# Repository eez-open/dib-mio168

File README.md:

### Ownership and License
The contributors are listed in CONTRIB.TXT.

Licenses | OSHWA UID
--|--
 | 

### Overview

The [EEZ DIB](https://github.com/eez-open/modular-psu) MIO168 module features multiple digital I/O, analog outputs and expansion connectors for carry various AFEs.

### Feature list

* On-board [STM32F446ZCT6](https://www.st.com/content/st_com/en/products/microcontrollers-microprocessors/stm32-32-bit-arm-cortex-mcus/stm32-high-performance-mcus/stm32f4-series/stm32f446/stm32f446zc.html) high-performance foundation line MCU, ARM Cortex-M4 with DSP and FPU, 256 KiB Flash, LQFP-144 package 
* 1 x 8-pin single row 3.81 mm connector (digital inputs)
* 1 x 16-pin dual row 3.81 mm I/O connector (digital and analog outputs)
* 2 x 10-pin ADIB 2.0 mm connectors
* 8 x protected digital inputs (3.3/5/24 V), 2 x fast/slow, 6 x slow
* 8 x digital outputs (low-side) with multiple protections, voltage clamp 42V, current limit 10 A
* 2 x PWM outputs (protected) or sensor bias power (+/-15 V, max. 10 mA)
* 2 x analog bipolar outputs (+/-5 V, +/-10 V, 0-5 V, 0-10 V). Voltage or current output with protection. 12-bit DAC, replaceable with pin compatible 14- or 16-bit version
* 2 x analog bipolar outputs +/-10 V. 12-bit DAC, replaceable with pin compatible 14- or 16-bit version
* On-board isolated power supply with +/-5.3 V outputs (with 4x multipliers), +/-15 V and +3.3 V LDO
* Firmware download via SPI
* Optional SWD for debugging
* I2C EEPROM for storing board specific parameters
* Dimensions: 146 x 95 mm, 4-layer PCB

### r3B1 prototype 3D model (without AFE installed)

### Firmware repository

https://github.com/eez-open/dib-mio168-fw  
The firmware download procedure is described in [Chapter 13.2](https://www.envox.eu/eez-bench-box-3/bb3-user-manual/13-firmware-upgrade/#bb3_man_module_upgrade) of the User Manual.  
The MIO168 module GUI is described in [Chapter 19](https://www.envox.eu/eez-bench-box-3/bb3-user-manual/19-mio168-mixed-input-output-module/) of the User Manual. 

### KiCad project (v7 or newer)

* [MIO168 r3B1](https://github.com/eez-open/dib-mio168/tree/master/EDA%20files/KiCad)

All symbols, footprints and 3D models used in the project can be found in the [EEZ-DIB Library](https://github.com/eez-open/eez-kicad-libraries) plugin for KiCad.

### Bill of materials

* [Download](https://github.com/eez-open/dib-mio168/tree/master/EDA%20files/KiCad/bom/ibom.html) as raw file _Interactive BOM_ (ibom.html) and open it locally in your browser.

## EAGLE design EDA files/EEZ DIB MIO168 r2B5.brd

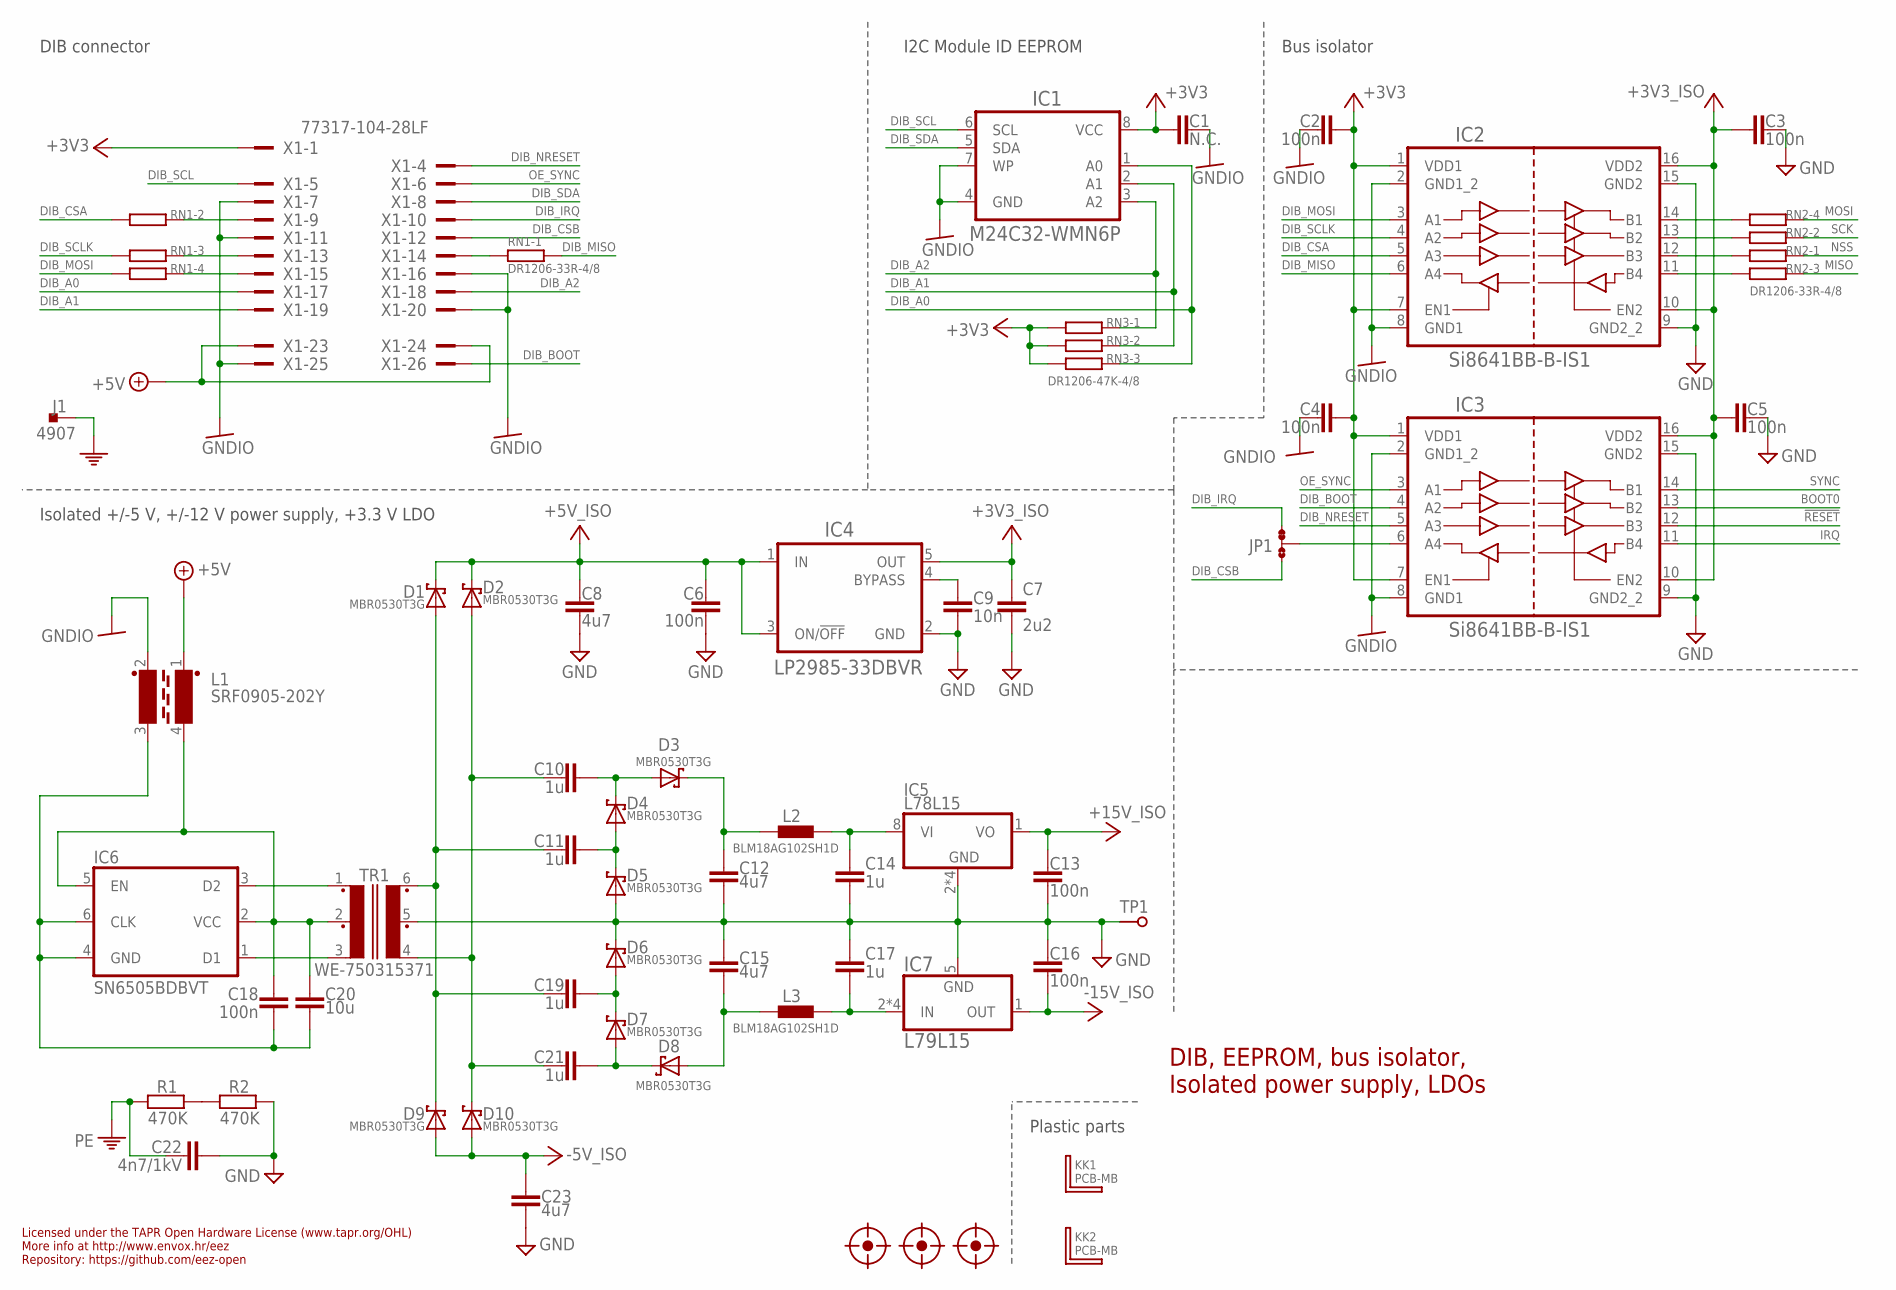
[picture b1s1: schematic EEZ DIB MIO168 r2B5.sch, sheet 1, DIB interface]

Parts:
C1: N.C.; C0603
C2, C3, C4, C5, C6, C13, C16, C18: 100n; C0603
C7: 2u2; C0805
C8, C12, C15, C23: 4u7; C0805
C9: 10n; C0805
C10, C11, C14, C17, C19, C21: 1u; C0805
C20: 10u; C1206
C22: 4n7/1kV; C1812
D1, D2, D3, D4, D5, D6, D7, D8, D9, D10: MBR0530T3G; SOD123
FM1, FM2, FM3: FIDUCIAL_2; FIDUCIAL_DUAL
IC1: M24C32-WMN6P; SOIC127P600X173-8N
IC2, IC3: Si8641BB-B-IS1; SOIC-16
IC4: LP2985-33DBVR; SOT95P270X145-5N
IC5: L78L15; SOIC127P600X173-8N
IC6: SN6505BDBVT; DBV0006A_N
IC7: L79L15; SOIC127P600X173-8N
J1: 4907; PCB_TAB-4907
JP1: JP3-CUT-0805-ROTATED; JP3-0805-CUT2
KK1, KK2: PCB-MB
L1: SRF0905-202Y; SRF0905
L2, L3: BLM18AG102SH1D; BEAD0603
R1, R2: 470K; R0805
RN1, RN2: DR1206-33R-4/8; CAY16
RN3: DR1206-47K-4/8; CAY16
TP1: PCB_TEST_TABSHIELD; PCB_SHIELD_TAB
TR1: WE-750315371; MURATA_78615
X1: 77317-104-28LF

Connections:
!RESET: IC3.12 (B3); also elsewhere on the board
+3V3: C1.2, C2.1, C4.1, IC1.8 (VCC), IC2.1 (VDD1), IC2.7 (EN1), IC3.1 (VDD1), IC3.7 (EN1), RN3.6 (2), RN3.7 (2), RN3.8 (2), X1.1
+3V3_ISO: C3.2, C5.2, C7.1, IC2.10 (EN2), IC2.16 (VDD2), IC3.10 (EN2), IC3.16 (VDD2), IC4.5 (OUT); also elsewhere on the board
+5V: L1.1, X1.23, X1.24
+5V_ISO: C6.1, C8.2, D1.C, D2.C, IC4.1 (IN), IC4.3 (ON/!OFF); also elsewhere on the board
+15V_ISO: C13.1, IC5.1 (VO); also elsewhere on the board
-5V_ISO: C23.2, D9.A, D10.A; also elsewhere on the board
-15V_IN: C17.1, IC7.2 (IN), IC7.3 (IN), IC7.6 (IN), IC7.7 (IN), L3.P$2 (2)
-15V_ISO: C16.2, IC7.1 (OUT); also elsewhere on the board
BOOT0: IC3.13 (B2); also elsewhere on the board
DIB_A0: IC1.1 (A0), RN3.3 (1), X1.17
DIB_A1: IC1.2 (A1), RN3.2 (1), X1.19
DIB_A2: IC1.3 (A2), RN3.1, X1.18
DIB_BOOT: IC3.4 (A2), X1.26
DIB_CSA: IC2.5 (A3), RN1.2 (1)
DIB_CSB: JP1.NO, X1.12
DIB_IRQ: JP1.NC, X1.10
DIB_MISO: IC2.6 (A4), RN1.1
DIB_MOSI: IC2.3 (A1), RN1.4 (1)
DIB_NRESET: IC3.5 (A3), X1.4
DIB_SCL: IC1.6 (SCL), X1.5
DIB_SCLK: IC2.4 (A2), RN1.3 (1)
DIB_SDA: IC1.5 (SDA), X1.8
GND: C3.1, C5.1, C6.2, C7.2, C8.1, C9.1, C12.2, C13.2, C14.1, C15.1, C16.1, C17.2, C22.2, C23.1, D5.A, D6.C, IC2.9 (GND2_2), IC2.15 (GND2), IC3.9 (GND2_2), IC3.15 (GND2), IC4.2 (GND), IC5.2 (GND), IC5.3 (GND), IC5.6 (GND), IC5.7 (GND), IC7.5 (GND), R2.2, TP1.1, TR1.5; also elsewhere on the board
GNDIO: C1.1, C2.2, C4.2, IC1.4 (GND), IC1.7 (WP), IC2.2 (GND1_2), IC2.8 (GND1), IC3.2 (GND1_2), IC3.8 (GND1), L1.2, X1.7, X1.11, X1.16, X1.20, X1.25
IRQ: IC3.11 (B4); also elsewhere on the board
MISO: RN2.6 (2); also elsewhere on the board
MOSI: RN2.5 (2); also elsewhere on the board
unnamed: IC3.6 (A4), JP1.COM
unnamed: IC2.14 (B1), RN2.4 (1)
unnamed: R1.2, R2.1
unnamed: C11.1, D4.A, D5.C
unnamed: IC6.3 (D2), TR1.1
unnamed: IC6.1 (D1), TR1.3
unnamed: C11.2, C19.2, D1.A, D9.C, TR1.6
unnamed: RN1.7 (2), X1.9
unnamed: C10.2, C21.2, D2.A, D10.C, TR1.4
unnamed: IC2.11 (B4), RN2.3 (1)
unnamed: C10.1, D3.A, D4.C
unnamed: RN1.6 (2), X1.13
unnamed: RN1.8 (2), X1.14
unnamed: RN1.5 (2), X1.15
unnamed: C19.1, D6.A, D7.C
unnamed: C21.1, D7.A, D8.C
unnamed: C9.2, IC4.4 (BYPASS)
unnamed: C14.2, IC5.8 (VI), L2.P$2 (2)
unnamed: IC2.13 (B2), RN2.2 (1)
unnamed: IC2.12 (B3), RN2.1
unnamed: C15.2, D8.A, L3.P$1 (1)
unnamed: C12.1, D3.C, L2.P$1 (1)
NSS: RN2.8 (2); also elsewhere on the board
OE_SYNC: IC3.3 (A1), X1.6
PE: C22.1, J1.1, J1.2, R1.1
SCK: RN2.7 (2); also elsewhere on the board
SN_GND: C18.2, C20.1, IC6.4 (GND), IC6.6 (CLK), L1.3
SN_VCC: C18.1, C20.2, IC6.2 (VCC), IC6.5 (EN), L1.4, TR1.2
SYNC: IC3.14 (B1); also elsewhere on the board

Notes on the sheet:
Licensed under the TAPR Open Hardware License (www.tapr.org/OHL)
Repository: https://github.com/eez-open
More info at http://www.envox.hr/eez
DIB, EEPROM, bus isolator, Isolated power supply, LDOs
Plastic parts
I2C Module ID EEPROM
Bus isolator
Isolated +/-5 V, +/-12 V power supply, +3.3 V LDO
DIB connector

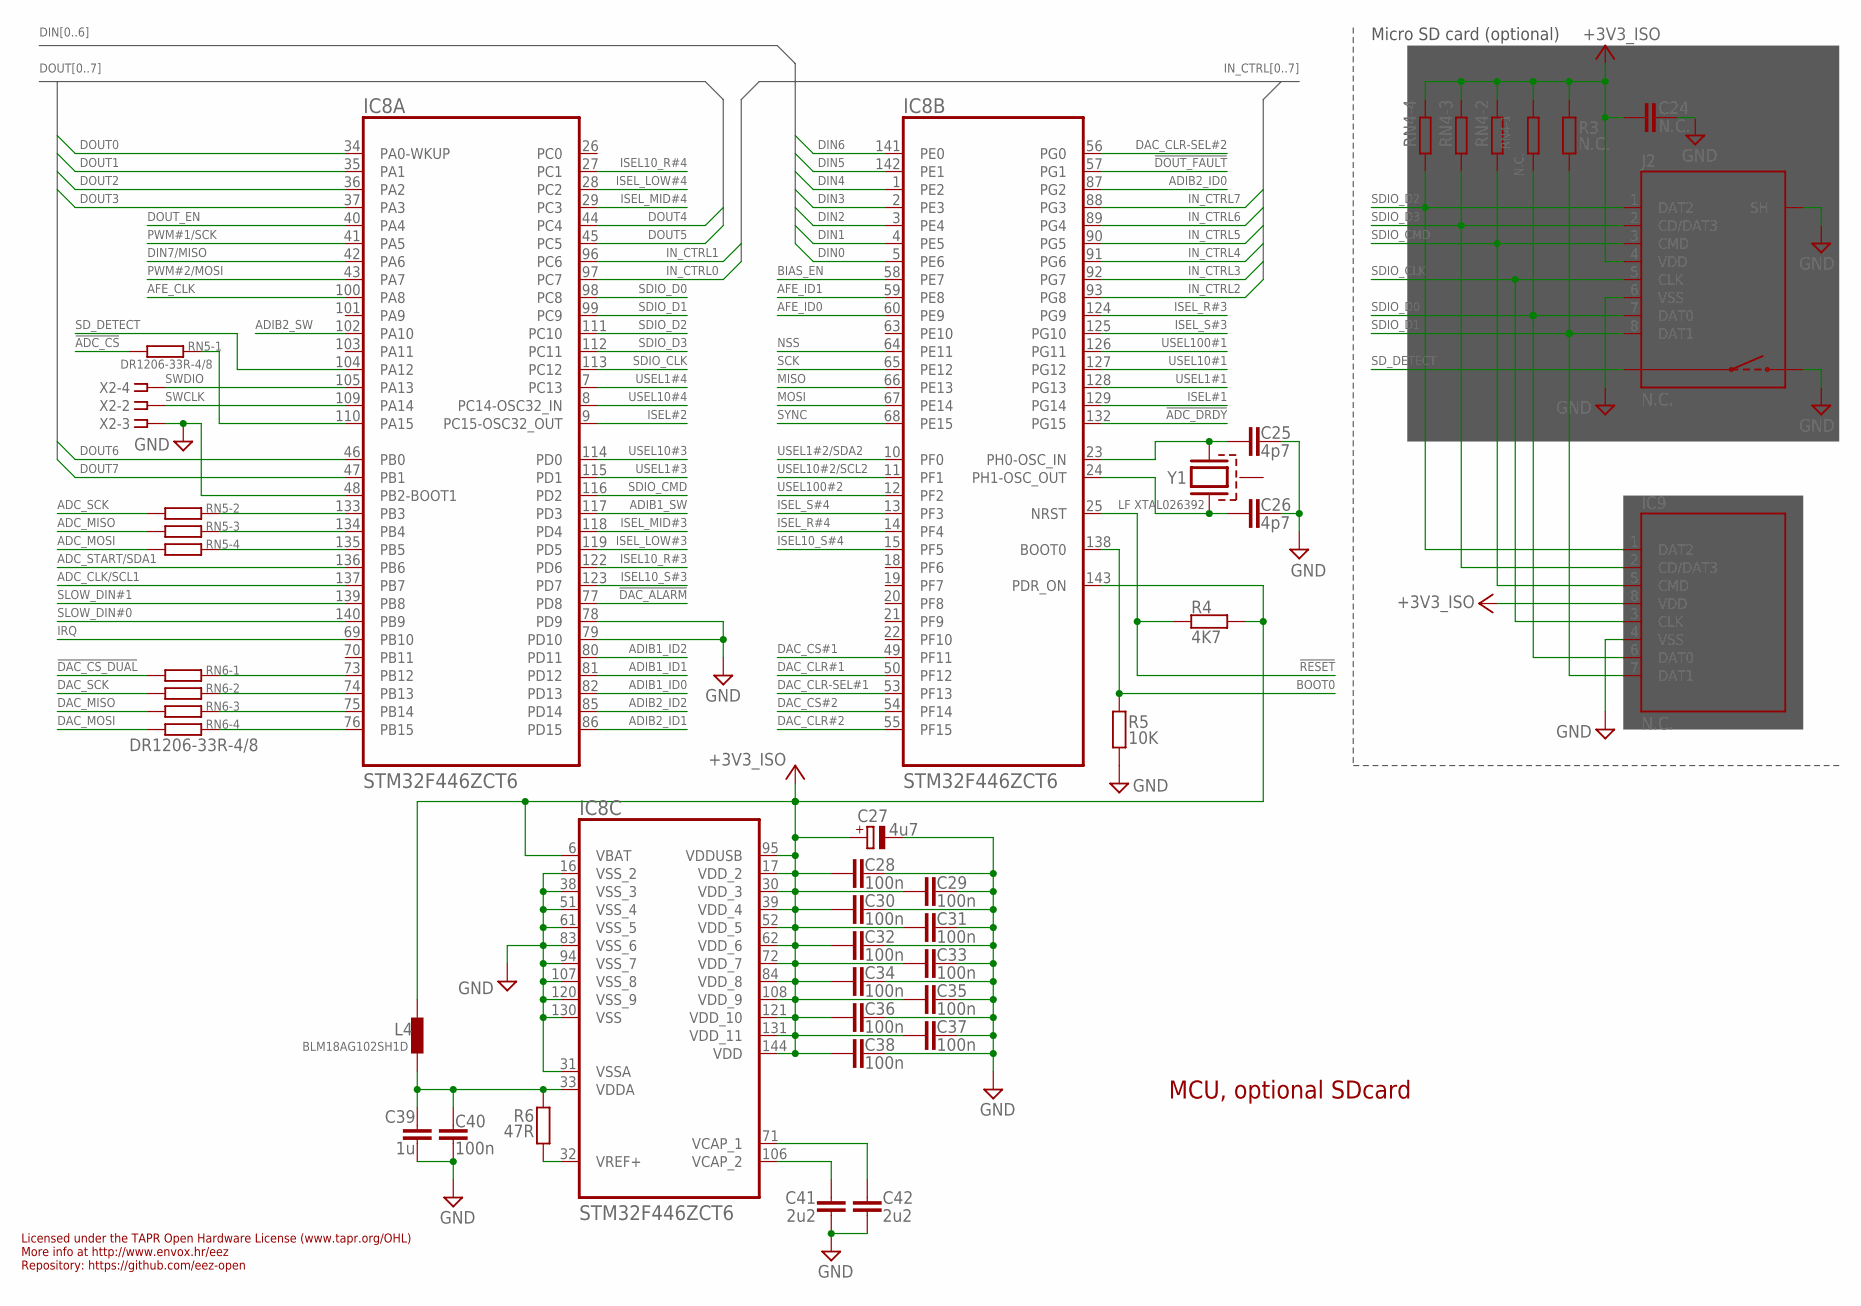
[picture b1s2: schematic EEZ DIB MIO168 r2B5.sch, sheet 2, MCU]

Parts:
C24: N.C.; C0805
C25, C26: 4p7; C0603
C27: 4u7; EC1206
C28, C29, C30, C31, C32, C33, C34, C35, C36, C37, C38, C40: 100n; C0603
C39: 1u; C0805
C41, C42: 2u2; C0805
IC8: STM32F446ZCT6; LQFP-144
IC9: N.C.; LGA8
J2: N.C.; 5033981892
L4: BLM18AG102SH1D; BEAD0603
R3: N.C.; R0805
R4: 4K7; R0805
R5: 10K; R0805
R6: 47R; R0805
RN4: N.C.; CAY16
RN5, RN6: DR1206-33R-4/8; CAY16
X2: N.C.; SSW-106-02-S-S
Y1: LF XTAL026392; 12SMX(B)

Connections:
!ADC_CS: RN5.1; also elsewhere on the board
!ADC_DRDY: IC8.132 (PG15); also elsewhere on the board
!DAC_ALARM: IC8.77 (PD8); also elsewhere on the board
!DAC_CS_DUAL: RN6.1; also elsewhere on the board
!DOUT_FAULT: IC8.57 (PG1); also elsewhere on the board
!RESET: IC8.25 (NRST), R4.2; also elsewhere on the board
+3V3_ISO: C24.1, C27.+, C28.1, C29.1, C30.1, C31.1, C32.1, C33.1, C34.1, C35.1, C36.1, C37.1, C38.1, IC8.6 (VBAT), IC8.17 (VDD_2), IC8.30 (VDD_3), IC8.39 (VDD_4), IC8.52 (VDD_5), IC8.62 (VDD_6), IC8.72 (VDD_7), IC8.84 (VDD_8), IC8.95 (VDDUSB), IC8.108 (VDD_9), IC8.121 (VDD_10), IC8.131 (VDD_11), IC8.143 (PDR_ON), IC8.144 (VDD), IC9.8 (VDD), J2.4 (VDD), L4.P$1 (1), R3.1, R4.1, RN4.1, RN4.2 (1), RN4.3 (1), RN4.4 (1); also elsewhere on the board
ADC_CLK/SCL1: IC8.137 (PB7); also elsewhere on the board
ADC_MISO: RN5.3 (1); also elsewhere on the board
ADC_MOSI: RN5.4 (1); also elsewhere on the board
ADC_SCK: RN5.2 (1); also elsewhere on the board
ADC_START/SDA1: IC8.136 (PB6); also elsewhere on the board
ADIB1_ID0: IC8.82 (PD13); also elsewhere on the board
ADIB1_ID1: IC8.81 (PD12); also elsewhere on the board
ADIB1_ID2: IC8.80 (PD11); also elsewhere on the board
ADIB1_SW: IC8.117 (PD3); also elsewhere on the board
ADIB2_ID0: IC8.87 (PG2); also elsewhere on the board
ADIB2_ID1: IC8.86 (PD15); also elsewhere on the board
ADIB2_ID2: IC8.85 (PD14); also elsewhere on the board
ADIB2_SW: IC8.102 (PA10); also elsewhere on the board
AFE_CLK: IC8.100 (PA8); also elsewhere on the board
AFE_ID0: IC8.60 (PE9); also elsewhere on the board
AFE_ID1: IC8.59 (PE8); also elsewhere on the board
BIAS_EN: IC8.58 (PE7); also elsewhere on the board
BOOT0: IC8.138 (BOOT0), R5.2; also elsewhere on the board
DAC_CLR#1: IC8.50 (PF12); also elsewhere on the board
DAC_CLR#2: IC8.55 (PF15); also elsewhere on the board
DAC_CLR-SEL#1: IC8.53 (PF13); also elsewhere on the board
DAC_CLR-SEL#2: IC8.56 (PG0); also elsewhere on the board
DAC_CS#1: IC8.49 (PF11); also elsewhere on the board
DAC_CS#2: IC8.54 (PF14); also elsewhere on the board
DAC_MISO: RN6.3 (1); also elsewhere on the board
DAC_MOSI: RN6.4 (1); also elsewhere on the board
DAC_SCK: RN6.2 (1); also elsewhere on the board
DIN0: IC8.5 (PE6); also elsewhere on the board
DIN1: IC8.4 (PE5); also elsewhere on the board
DIN2: IC8.3 (PE4); also elsewhere on the board
DIN3: IC8.2 (PE3); also elsewhere on the board
DIN4: IC8.1 (PE2); also elsewhere on the board
DIN5: IC8.142 (PE1); also elsewhere on the board
DIN6: IC8.141 (PE0); also elsewhere on the board
DIN7/MISO: IC8.42 (PA6); also elsewhere on the board
DOUT0: IC8.34 (PA0-WKUP); also elsewhere on the board
DOUT1: IC8.35 (PA1); also elsewhere on the board
DOUT2: IC8.36 (PA2); also elsewhere on the board
DOUT3: IC8.37 (PA3); also elsewhere on the board
DOUT4: IC8.44 (PC4); also elsewhere on the board
DOUT5: IC8.45 (PC5); also elsewhere on the board
DOUT6: IC8.46 (PB0); also elsewhere on the board
DOUT7: IC8.47 (PB1); also elsewhere on the board
DOUT_EN: IC8.40 (PA4); also elsewhere on the board
GND: C24.2, C25.1, C26.1, C27.-, C28.2, C29.2, C30.2, C31.2, C32.2, C33.2, C34.2, C35.2, C36.2, C37.2, C38.2, C39.2, C40.2, C41.1, C42.1, IC8.16 (VSS_2), IC8.31 (VSSA), IC8.38 (VSS_3), IC8.48 (PB2-BOOT1), IC8.51 (VSS_4), IC8.61 (VSS_5), IC8.78 (PD9), IC8.79 (PD10), IC8.83 (VSS_6), IC8.94 (VSS_7), IC8.107 (VSS_8), IC8.120 (VSS_9), IC8.130 (VSS), IC9.4 (VSS), J2.6 (VSS), J2.S (SH), J2.S1 (SH), J2.S2 (SH), J2.SW2, R5.1, X2.3; also elsewhere on the board
IN_CTRL0: IC8.97 (PC7); also elsewhere on the board
IN_CTRL1: IC8.96 (PC6); also elsewhere on the board
IN_CTRL2: IC8.93 (PG8); also elsewhere on the board
IN_CTRL3: IC8.92 (PG7); also elsewhere on the board
IN_CTRL4: IC8.91 (PG6); also elsewhere on the board
IN_CTRL5: IC8.90 (PG5); also elsewhere on the board
IN_CTRL6: IC8.89 (PG4); also elsewhere on the board
IN_CTRL7: IC8.88 (PG3); also elsewhere on the board
IRQ: IC8.69 (PB10); also elsewhere on the board
ISEL10_R#3: IC8.122 (PD6); also elsewhere on the board
ISEL10_R#4: IC8.27 (PC1); also elsewhere on the board
ISEL10_S#3: IC8.123 (PD7); also elsewhere on the board
ISEL10_S#4: IC8.15 (PF5); also elsewhere on the board
ISEL#1: IC8.129 (PG14); also elsewhere on the board
ISEL#2: IC8.9 (PC15-OSC32_OUT); also elsewhere on the board
ISEL_LOW#3: IC8.119 (PD5); also elsewhere on the board
ISEL_LOW#4: IC8.28 (PC2); also elsewhere on the board
ISEL_MID#3: IC8.118 (PD4); also elsewhere on the board
ISEL_MID#4: IC8.29 (PC3); also elsewhere on the board
ISEL_R#3: IC8.124 (PG9); also elsewhere on the board
ISEL_R#4: IC8.14 (PF4); also elsewhere on the board
ISEL_S#3: IC8.125 (PG10); also elsewhere on the board
ISEL_S#4: IC8.13 (PF3); also elsewhere on the board
MISO: IC8.66 (PE13); also elsewhere on the board
MOSI: IC8.67 (PE14); also elsewhere on the board
unnamed: IC8.110 (PA15), RN5.8 (2)
unnamed: IC8.133 (PB3), RN5.7 (2)
unnamed: IC8.134 (PB4), RN5.6 (2)
unnamed: C41.2, IC8.106 (VCAP_2)
unnamed: IC8.135 (PB5), RN5.5 (2)
unnamed: C42.2, IC8.71 (VCAP_1)
unnamed: C39.1, C40.1, IC8.33 (VDDA), L4.P$2 (2), R6.1
unnamed: IC8.32 (VREF+), R6.2
unnamed: IC8.73 (PB12), RN6.8 (2)
unnamed: IC8.74 (PB13), RN6.7 (2)
unnamed: IC8.75 (PB14), RN6.6 (2)
unnamed: IC8.76 (PB15), RN6.5 (2)
NSS: IC8.64 (PE11); also elsewhere on the board
PWM#1/SCK: IC8.41 (PA5); also elsewhere on the board
PWM#2/MOSI: IC8.43 (PA7); also elsewhere on the board
RCC_OSC_IN: C25.2, IC8.23 (PH0-OSC_IN), Y1.3 (2)
RCC_OSC_OUT: C26.2, IC8.24 (PH1-OSC_OUT), Y1.1
SCK: IC8.65 (PE12); also elsewhere on the board
SDIO_CLK: IC8.113 (PC12), IC9.3 (CLK), J2.5 (CLK)
SDIO_CMD: IC8.116 (PD2), IC9.5 (CMD), J2.3 (CMD), RN4.7 (2)
SDIO_D0: IC8.98 (PC8), IC9.6 (DAT0), J2.7 (DAT0), RN4.8 (2)
SDIO_D1: IC8.99 (PC9), IC9.7 (DAT1), J2.8 (DAT1), R3.2
SDIO_D2: IC8.111 (PC10), IC9.1 (DAT2), J2.1 (DAT2), RN4.5 (2)
SDIO_D3: IC8.112 (PC11), IC9.2 (CD/DAT3), J2.2 (CD/DAT3), RN4.6 (2)
SD_DETECT: IC8.104 (PA12), J2.SW1
SLOW_DIN#0: IC8.140 (PB9); also elsewhere on the board
SLOW_DIN#1: IC8.139 (PB8); also elsewhere on the board
SWCLK: IC8.109 (PA14), X2.2
SWDIO: IC8.105 (PA13), X2.4
SYNC: IC8.68 (PE15); also elsewhere on the board
USEL1#1: IC8.128 (PG13); also elsewhere on the board
USEL1#2/SDA2: IC8.10 (PF0); also elsewhere on the board
USEL1#3: IC8.115 (PD1); also elsewhere on the board
USEL1#4: IC8.7 (PC13); also elsewhere on the board
USEL10#1: IC8.127 (PG12); also elsewhere on the board
USEL10#2/SCL2: IC8.11 (PF1); also elsewhere on the board
USEL10#3: IC8.114 (PD0); also elsewhere on the board
USEL10#4: IC8.8 (PC14-OSC32_IN); also elsewhere on the board
USEL100#1: IC8.126 (PG11); also elsewhere on the board
USEL100#2: IC8.12 (PF2); also elsewhere on the board

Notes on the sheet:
Licensed under the TAPR Open Hardware License (www.tapr.org/OHL)
Repository: https://github.com/eez-open
More info at http://www.envox.hr/eez
MCU, optional SDcard
Micro SD card (optional)

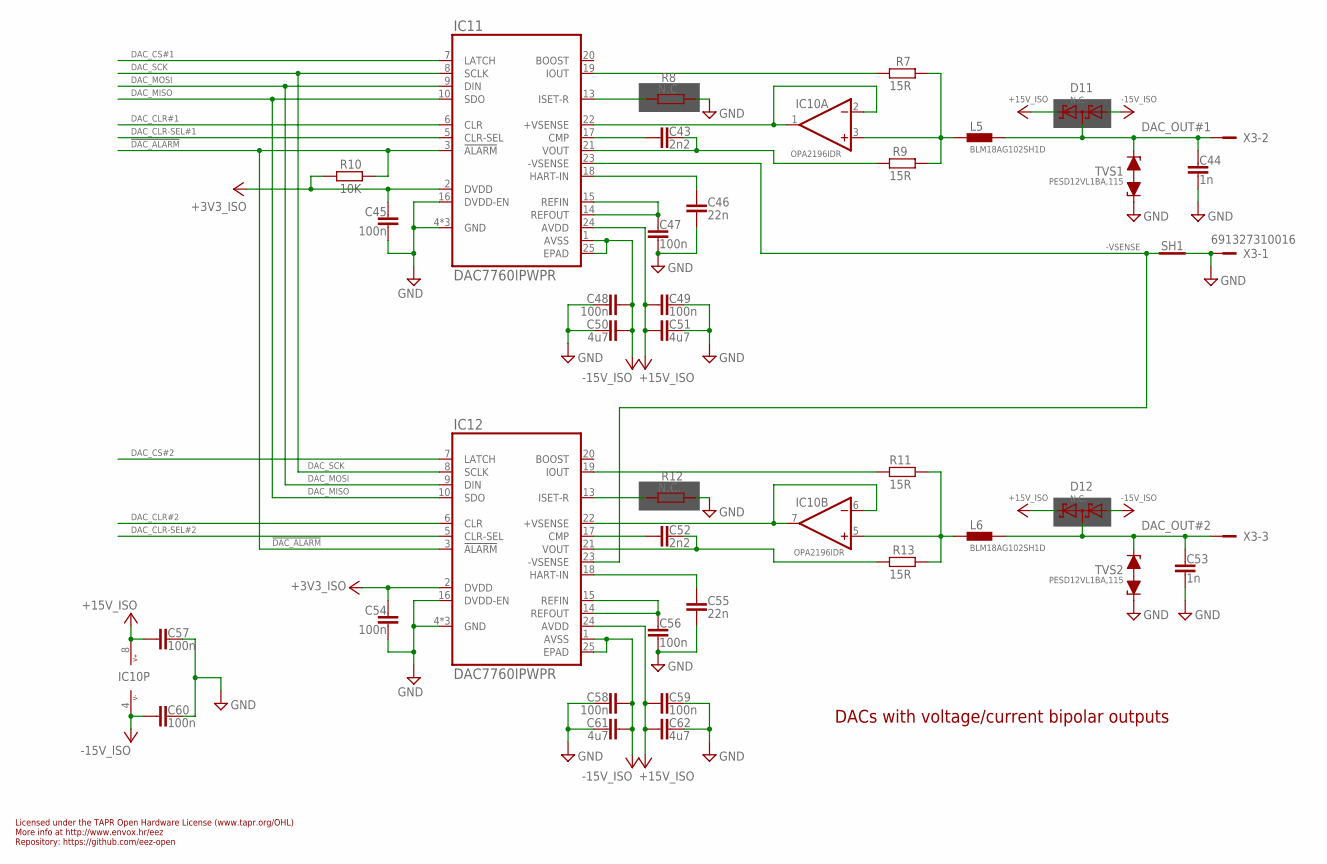
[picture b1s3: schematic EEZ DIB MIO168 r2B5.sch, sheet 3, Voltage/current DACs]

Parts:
C43, C52: 2n2; C0805
C44, C53: 1n; C0805
C45, C47, C48, C49, C54, C56, C57, C58, C59, C60: 100n; C0603
C46, C55: 22n; C0805
C50, C51, C61, C62: 4u7; C0805
D11, D12: N.C.; SOT23
IC10: OPA2196IDR; SOIC127P600X173-8N
IC11, IC12: DAC7760IPWPR; PWP24
L5, L6: BLM18AG102SH1D; BEAD0603
R7, R9, R11, R13: 15R; R0805
R8, R12: N.C.; R0805
R10: 10K; R0805
SH1: SHORTNOHOLE; SHORT_NOHOLE
TVS1, TVS2: PESD12VL1BA,115; SOD323-BIDIR
X3: 691327310016

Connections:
!DAC_ALARM: IC11.3 (!ALARM), IC12.3 (!ALARM), R10.2; also elsewhere on the board
+3V3_ISO: C45.1, C54.1, IC11.2 (DVDD), IC12.2 (DVDD), R10.1; also elsewhere on the board
+15V_ISO: C49.1, C51.2, C57.1, C59.1, C62.2, D11.2 (C2), D12.2 (C2), IC10.8 (V+), IC11.24 (AVDD), IC12.24 (AVDD); also elsewhere on the board
+VSENSE1: IC10.1 (OUT), IC10.2 (-IN), IC11.22 (+VSENSE)
+VSENSE2: IC10.6 (-IN), IC10.7 (OUT), IC12.22 (+VSENSE)
-15V_ISO: C48.1, C50.2, C58.1, C60.1, C61.2, D11.1 (A1), D12.1 (A1), IC10.4 (V-), IC11.1 (AVSS), IC11.25 (EPAD), IC12.1 (AVSS), IC12.25 (EPAD); also elsewhere on the board
-VSENSE: IC11.23 (-VSENSE), IC12.23 (-VSENSE), SH1.2 (GND_B); also elsewhere on the board
DAC_CLR#1: IC11.6 (CLR); also elsewhere on the board
DAC_CLR#2: IC12.6 (CLR); also elsewhere on the board
DAC_CLR-SEL#1: IC11.5 (CLR-SEL); also elsewhere on the board
DAC_CLR-SEL#2: IC12.5 (CLR-SEL); also elsewhere on the board
DAC_CS#1: IC11.7 (LATCH); also elsewhere on the board
DAC_CS#2: IC12.7 (LATCH); also elsewhere on the board
DAC_MISO: IC11.10 (SDO), IC12.10 (SDO); also elsewhere on the board
DAC_MOSI: IC11.9 (DIN), IC12.9 (DIN); also elsewhere on the board
DAC_OUT#1: C44.1, D11.3 (C1A2), L5.P$2 (2), TVS1.C2 (2), X3.2; also elsewhere on the board
DAC_OUT#2: C53.1, D12.3 (C1A2), L6.P$2 (2), TVS2.C2 (2), X3.3; also elsewhere on the board
DAC_SCK: IC11.8 (SCLK), IC12.8 (SCLK); also elsewhere on the board
GND: C44.2, C45.2, C46.1, C47.2, C48.2, C49.2, C50.1, C51.1, C53.2, C54.2, C55.1, C56.2, C57.2, C58.2, C59.2, C60.2, C61.1, C62.1, IC11.4 (GND), IC11.11 (GND), IC11.12 (GND), IC11.16 (DVDD-EN), IC12.4 (GND), IC12.11 (GND), IC12.12 (GND), IC12.16 (DVDD-EN), R8.1, R12.1, SH1.1 (GND_A), TVS1.C1 (1), TVS2.C1 (1), X3.1; also elsewhere on the board
HART#1: C46.2, IC11.18 (HART-IN)
HART#2: C55.2, IC12.18 (HART-IN)
unnamed: C52.2, IC12.17 (CMP)
unnamed: C52.1, IC12.21 (VOUT), R13.2
unnamed: IC10.5 (+IN), L6.P$1 (1), R11.1, R13.1
unnamed: IC12.19 (IOUT), R11.2
unnamed: C56.1, IC12.14 (REFOUT), IC12.15 (REFIN)
unnamed: C43.2, IC11.17 (CMP)
unnamed: IC10.3 (+IN), L5.P$1 (1), R7.1, R9.1
unnamed: C47.1, IC11.14 (REFOUT), IC11.15 (REFIN)
unnamed: IC12.13 (ISET-R), R12.2
unnamed: IC11.13 (ISET-R), R8.2
unnamed: C43.1, IC11.21 (VOUT), R9.2
unnamed: IC11.19 (IOUT), R7.2

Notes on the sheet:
Licensed under the TAPR Open Hardware License (www.tapr.org/OHL)
Repository: https://github.com/eez-open
More info at http://www.envox.hr/eez
DACs with voltage/current bipolar outputs

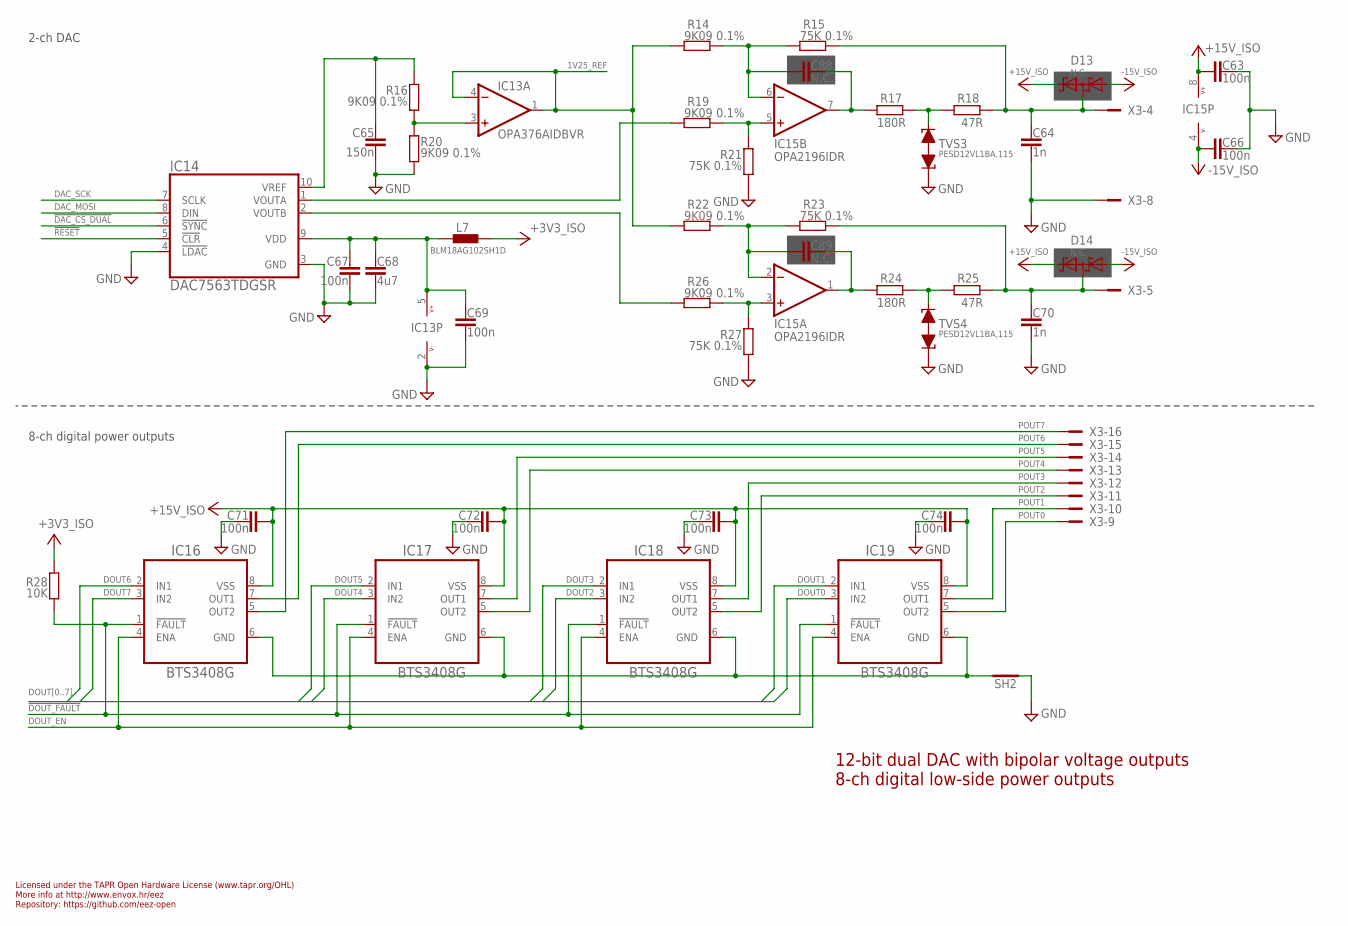
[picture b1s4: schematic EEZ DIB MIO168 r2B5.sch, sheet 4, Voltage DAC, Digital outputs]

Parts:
C63, C66, C67, C69, C71, C72, C73, C74: 100n; C0603
C64, C70: 1n; C0805
C65: 150n; C0805
C68: 4u7; C0805
C88, C89: N.C.; C0805
D13, D14: N.C.; SOT23
IC13: OPA376AIDBVR; DBV5
IC14: DAC7563TDGSR; DGS10
IC15: OPA2196IDR; SOIC127P600X173-8N
IC16, IC17, IC18, IC19: BTS3408G; SOIC127P600X173-8N
L7: BLM18AG102SH1D; BEAD0603
R14, R16, R19, R20, R22, R26: 9K09 0.1%; R0805
R15, R21, R23, R27: 75K 0.1%; R0805
R17, R24: 180R; R0805
R18, R25: 47R; R0805
R28: 10K; R0805
SH2: SHORTNOHOLE; SHORT_NOHOLE
TVS3, TVS4: PESD12VL1BA,115; SOD323-BIDIR
X3: 691327310016

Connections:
1V25_REF: IC13.1 (OUT), IC13.4 (-IN), R14.2, R22.2
2V5_REF: C65.2, IC14.10 (VREF), R16.1
!DAC_CS_DUAL: IC14.6 (!SYNC); also elsewhere on the board
!DOUT_FAULT: IC16.1 (!FAULT), IC17.1 (!FAULT), IC18.1 (!FAULT), IC19.1 (!FAULT), R28.2; also elsewhere on the board
!RESET: IC14.5 (!CLR); also elsewhere on the board
+3V3_ISO: L7.P$2 (2), R28.1; also elsewhere on the board
+15V_ISO: C63.1, C71.2, C72.2, C73.2, C74.2, D13.2 (C2), D14.2 (C2), IC15.8 (V+), IC16.8 (VSS), IC17.8 (VSS), IC18.8 (VSS), IC19.8 (VSS); also elsewhere on the board
-15V_ISO: C66.1, D13.1 (A1), D14.1 (A1), IC15.4 (V-); also elsewhere on the board
DAC_MOSI: IC14.8 (DIN); also elsewhere on the board
DAC_SCK: IC14.7 (SCLK); also elsewhere on the board
DOUT0: IC19.3 (IN2); also elsewhere on the board
DOUT1: IC19.2 (IN1); also elsewhere on the board
DOUT2: IC18.3 (IN2); also elsewhere on the board
DOUT3: IC18.2 (IN1); also elsewhere on the board
DOUT4: IC17.3 (IN2); also elsewhere on the board
DOUT5: IC17.2 (IN1); also elsewhere on the board
DOUT6: IC16.2 (IN1); also elsewhere on the board
DOUT7: IC16.3 (IN2); also elsewhere on the board
DOUT_EN: IC16.4 (ENA), IC17.4 (ENA), IC18.4 (ENA), IC19.4 (ENA); also elsewhere on the board
GND: C63.2, C64.2, C65.1, C66.2, C67.2, C68.1, C69.2, C70.2, C71.1, C72.1, C73.1, C74.1, IC13.2 (V-), IC14.3 (GND), IC14.4 (!LDAC), R20.2, R21.2, R27.2, SH2.1 (GND_A), TVS3.C1 (1), TVS4.C1 (1), X3.8; also elsewhere on the board
ISET1: R17.2, R18.1, TVS3.C2 (2)
ISET2: R24.2, R25.1, TVS4.C2 (2)
unnamed: IC16.6 (GND), IC17.6 (GND), IC18.6 (GND), IC19.6 (GND), SH2.2 (GND_B)
unnamed: IC15.5 (+IN), R19.1, R21.1
unnamed: C88.1, IC15.6 (-IN), R14.1, R15.2
unnamed: C88.2, IC15.7 (OUT), R17.1
unnamed: IC15.3 (+IN), R26.1, R27.1
unnamed: C89.1, IC15.2 (-IN), R22.1, R23.2
unnamed: C89.2, IC15.1 (OUT), R24.1
unnamed: IC13.3 (+IN), R16.2, R20.1
unnamed: IC14.1 (VOUTA), R19.2
unnamed: IC14.2 (VOUTB), R26.2
unnamed: C67.1, C68.2, C69.1, IC13.5 (V+), IC14.9 (VDD), L7.P$1 (1)
unnamed: C70.1, D14.3 (C1A2), R23.1, R25.2, X3.5
unnamed: C64.1, D13.3 (C1A2), R15.1, R18.2, X3.4
POUT0: IC19.5 (OUT2), X3.9
POUT1: IC19.7 (OUT1), X3.10
POUT2: IC18.5 (OUT2), X3.11
POUT3: IC18.7 (OUT1), X3.12
POUT4: IC17.5 (OUT2), X3.13
POUT5: IC17.7 (OUT1), X3.14
POUT6: IC16.7 (OUT1), X3.15
POUT7: IC16.5 (OUT2), X3.16

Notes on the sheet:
Licensed under the TAPR Open Hardware License (www.tapr.org/OHL)
Repository: https://github.com/eez-open
More info at http://www.envox.hr/eez
12-bit dual DAC with bipolar voltage outputs 8-ch digital low-side power outputs
8-ch digital power outputs
2-ch DAC

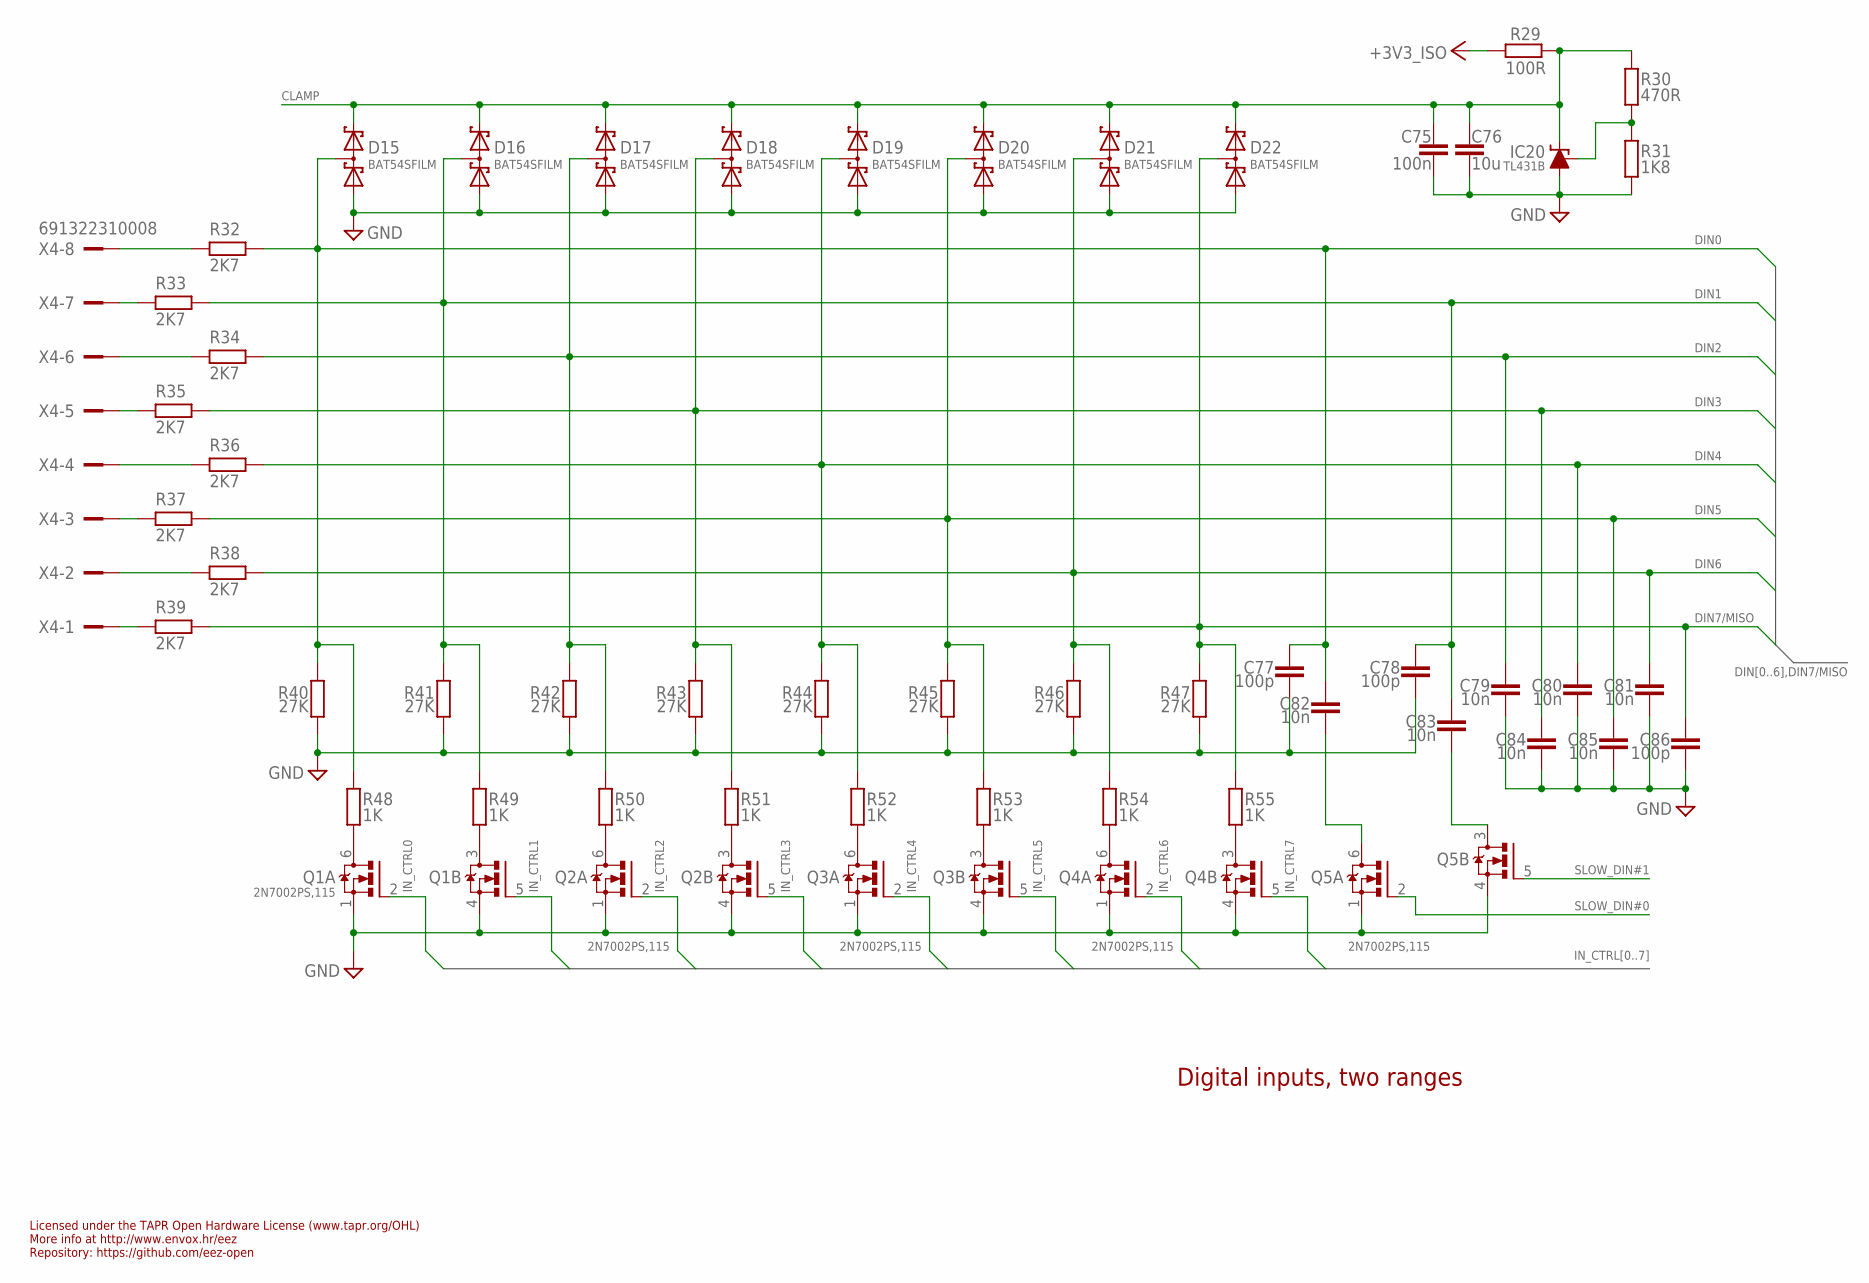
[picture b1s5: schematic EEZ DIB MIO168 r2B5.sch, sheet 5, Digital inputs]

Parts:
C75: 100n; C0603
C76: 10u; C1206
C77, C78, C86: 100p; C0805
C79, C80, C81, C82, C83, C84, C85: 10n; C0805
D15, D16, D17, D18, D19, D20, D21, D22: BAT54SFILM; SOT23
IC20: TL431B; SOT103P240X110-3N
Q1, Q2, Q3, Q4, Q5: 2N7002PS,115; SC88
R29: 100R; R0805
R30: 470R; R0805
R31: 1K8; R0805
R32, R33, R34, R35, R36, R37, R38, R39: 2K7; R1206
R40, R41, R42, R43, R44, R45, R46, R47: 27K; R0805
R48, R49, R50, R51, R52, R53, R54, R55: 1K; R0805
X4: 691322310008

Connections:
+3V3_ISO: R29.1; also elsewhere on the board
CLAMP: C75.1, C76.1, D15.2 (C2), D16.2 (C2), D17.2 (C2), D18.2 (C2), D19.2 (C2), D20.2 (C2), D21.2 (C2), D22.2 (C2), IC20.1 (C), R29.2, R30.1; also elsewhere on the board
DIN0: C77.1, C82.1, D15.3 (C1A2), R32.2, R40.2, R48.1; also elsewhere on the board
DIN1: C78.1, C83.1, D16.3 (C1A2), R33.2, R41.2, R49.1; also elsewhere on the board
DIN2: C79.1, D17.3 (C1A2), R34.2, R42.2, R50.1; also elsewhere on the board
DIN3: C84.1, D18.3 (C1A2), R35.2, R43.2, R51.1; also elsewhere on the board
DIN4: C80.1, D19.3 (C1A2), R36.2, R44.2, R52.1; also elsewhere on the board
DIN5: C85.1, D20.3 (C1A2), R37.2, R45.2, R53.1; also elsewhere on the board
DIN6: C81.1, D21.3 (C1A2), R38.2, R46.2, R54.1; also elsewhere on the board
DIN7/MISO: C86.1, D22.3 (C1A2), R39.2, R47.2, R55.1; also elsewhere on the board
GND: C75.2, C76.2, C77.2, C78.2, C79.2, C80.2, C81.2, C84.2, C85.2, C86.2, D15.1 (A1), D16.1 (A1), D17.1 (A1), D18.1 (A1), D19.1 (A1), D20.1 (A1), D21.1 (A1), D22.1 (A1), IC20.3 (A), Q1.1 (S), Q1.4 (S), Q2.1 (S), Q2.4 (S), Q3.1 (S), Q3.4 (S), Q4.1 (S), Q4.4 (S), Q5.1 (S), Q5.4 (S), R31.2, R40.1, R41.1, R42.1, R43.1, R44.1, R45.1, R46.1, R47.1; also elsewhere on the board
IN_CTRL0: Q1.2 (G); also elsewhere on the board
IN_CTRL1: Q1.5 (G); also elsewhere on the board
IN_CTRL2: Q2.2 (G); also elsewhere on the board
IN_CTRL3: Q2.5 (G); also elsewhere on the board
IN_CTRL4: Q3.2 (G); also elsewhere on the board
IN_CTRL5: Q3.5 (G); also elsewhere on the board
IN_CTRL6: Q4.2 (G); also elsewhere on the board
IN_CTRL7: Q4.5 (G); also elsewhere on the board
unnamed: IC20.2 (R), R30.2, R31.1
unnamed: Q1.6 (D), R48.2
unnamed: Q1.3 (D), R49.2
unnamed: Q2.6 (D), R50.2
unnamed: Q2.3 (D), R51.2
unnamed: R33.1, X4.7
unnamed: Q3.6 (D), R52.2
unnamed: Q3.3 (D), R53.2
unnamed: Q4.6 (D), R54.2
unnamed: Q4.3 (D), R55.2
unnamed: C82.2, Q5.6 (D)
unnamed: R32.1, X4.8
unnamed: R34.1, X4.6
unnamed: R35.1, X4.5
unnamed: C83.2, Q5.3 (D)
unnamed: R36.1, X4.4
unnamed: R38.1, X4.2
unnamed: R39.1, X4.1
unnamed: R37.1, X4.3
SLOW_DIN#0: Q5.2 (G); also elsewhere on the board
SLOW_DIN#1: Q5.5 (G); also elsewhere on the board

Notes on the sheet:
Licensed under the TAPR Open Hardware License (www.tapr.org/OHL)
Repository: https://github.com/eez-open
More info at http://www.envox.hr/eez
Digital inputs, two ranges

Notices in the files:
parts and their libraries:
EEZ_DIB: This work is licensed under the TAPR Open Hardware License.
